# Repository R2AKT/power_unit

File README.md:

License addendum - https://github.com/R2AKT/power_unit/blob/main/Addendum.txt
# power_unit

Power control unit. For Mega-80 (Mega-580) DIY 8-bit micro-computer - https://github.com/R2AKT/Mega-80.
ATX PSU control based on 'ISA 8-bit Backplane' (https://github.com/skiselev/isa8_backplane).

Status - Tested.

Плата питания. Для самодельной 8-битной микро-ЭВМ - https://github.com/R2AKT/Mega-80.
Управление блоком питания ATX на основе 'ISA 8-bit Backplane' (https://github.com/skiselev/isa8_backplane).

Статус - Проверено.

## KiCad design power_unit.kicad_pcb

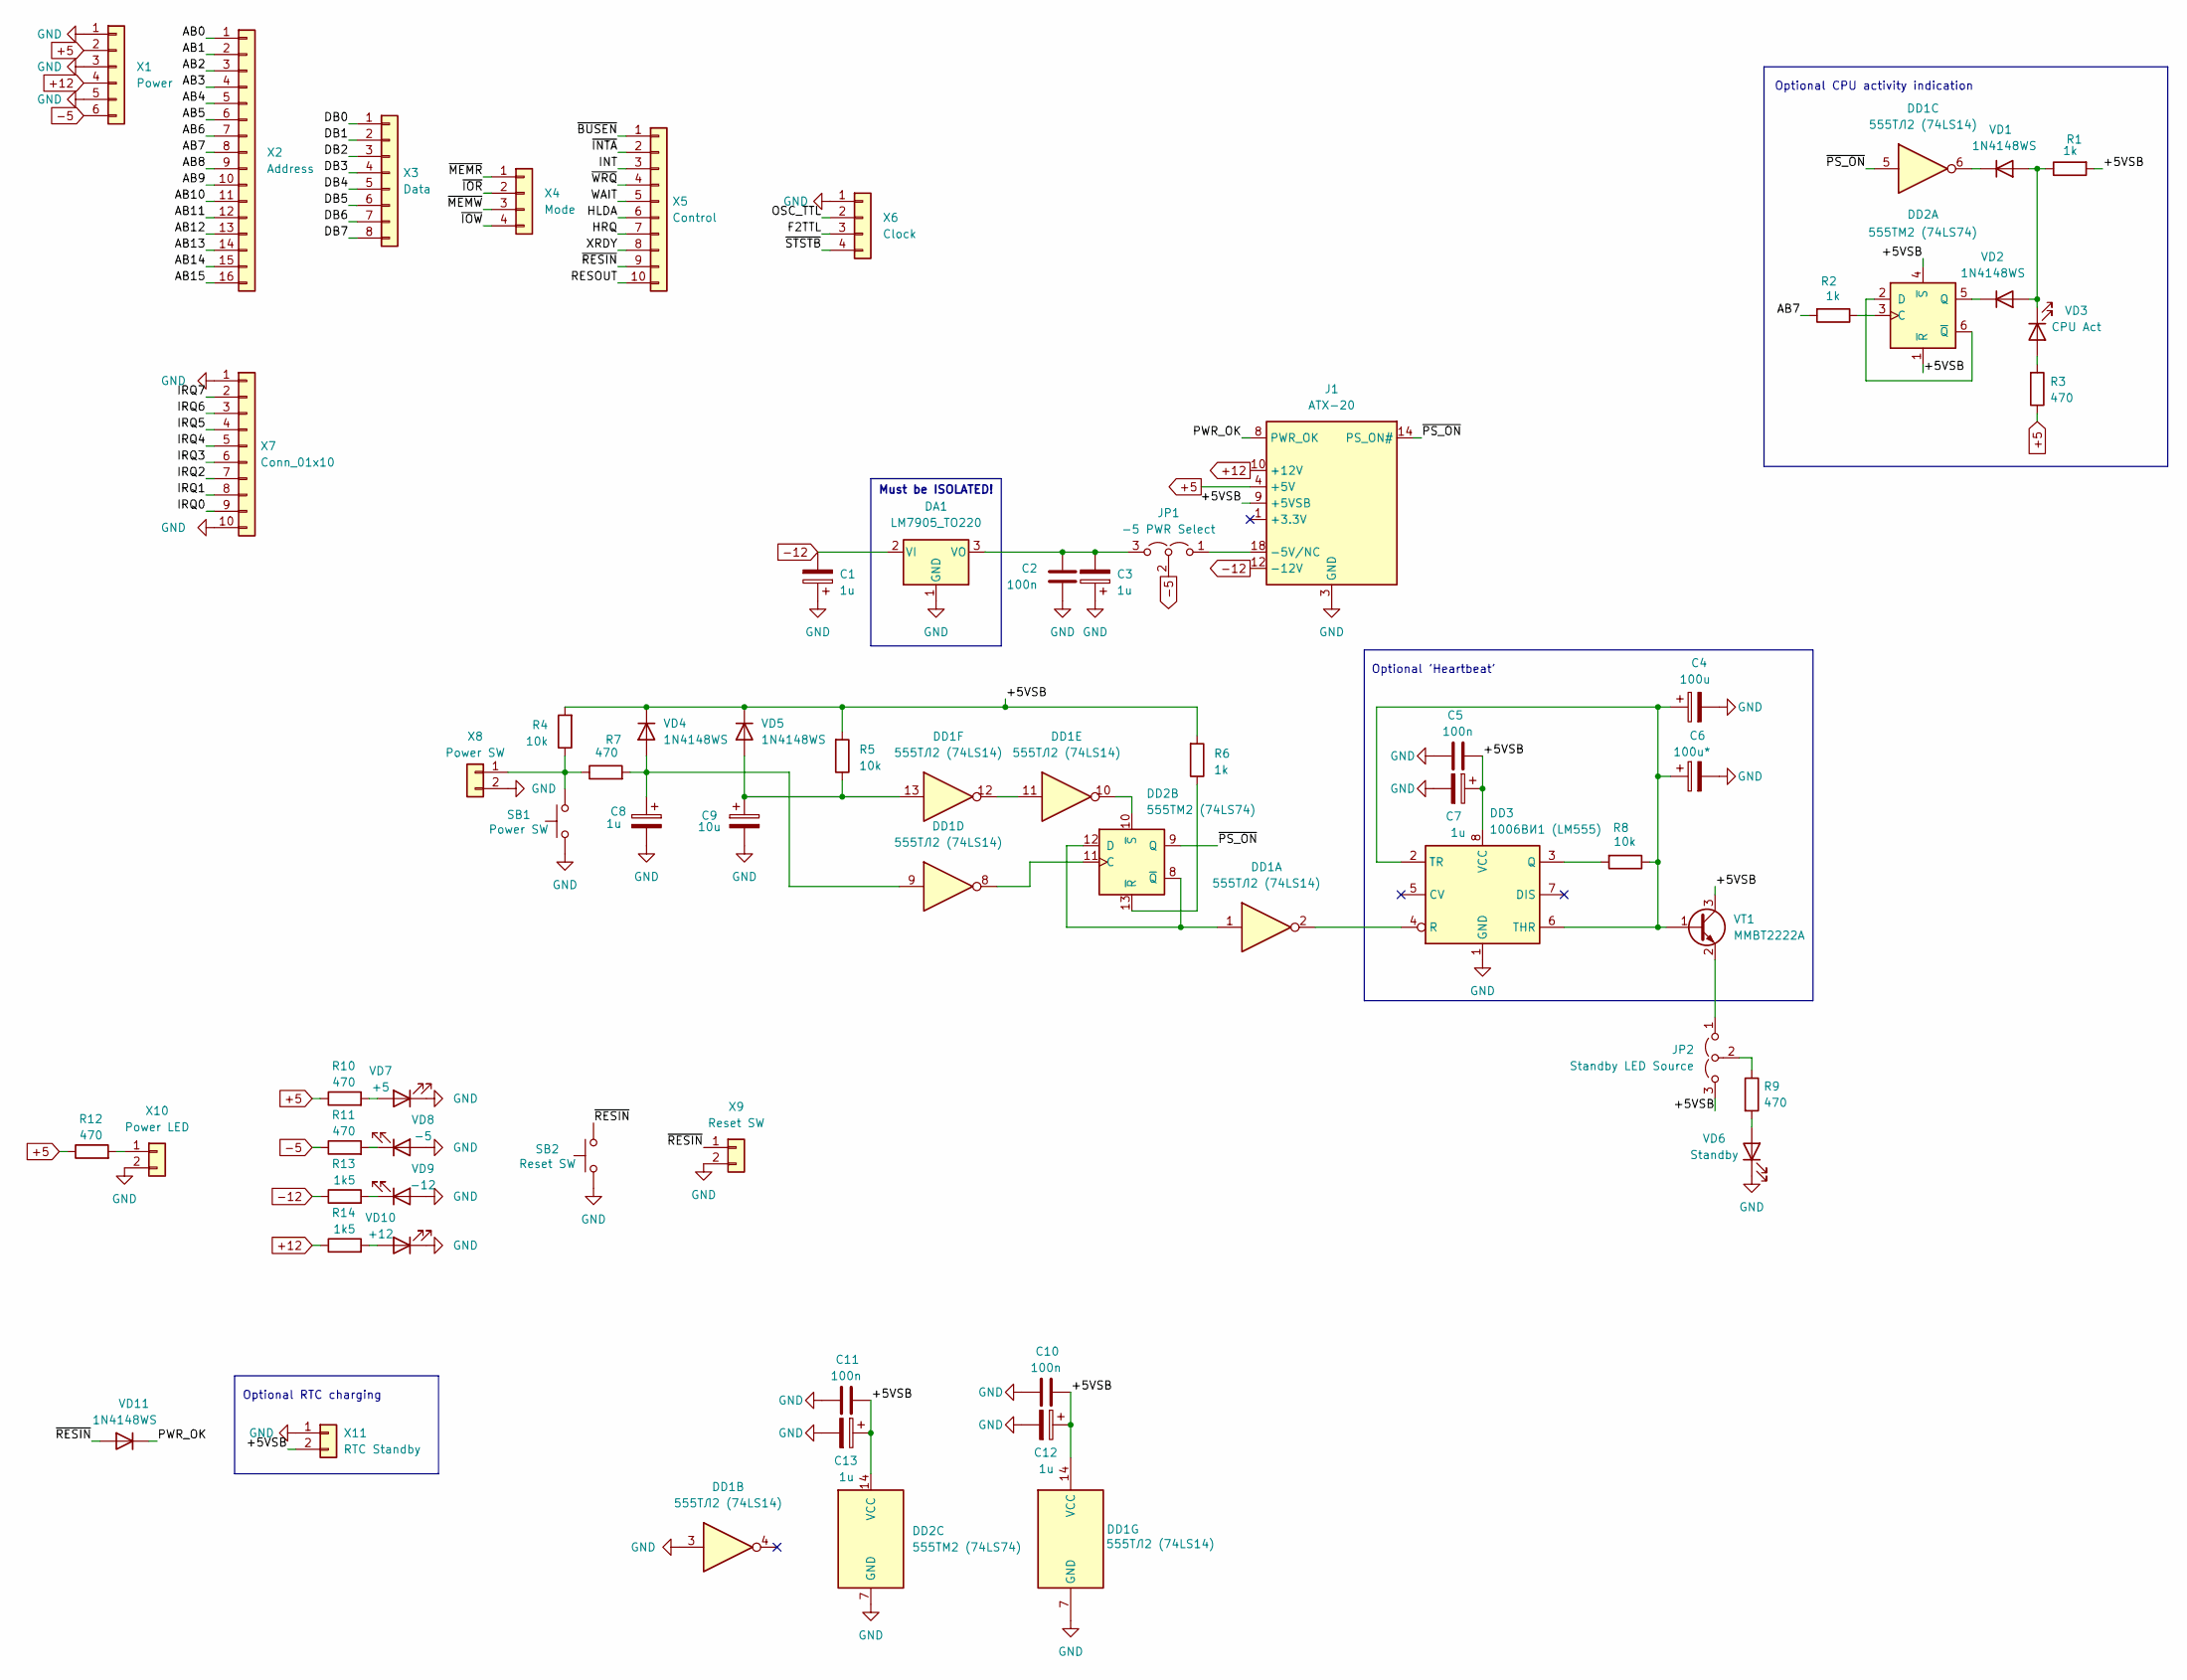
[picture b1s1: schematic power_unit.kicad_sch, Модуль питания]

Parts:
C1, C3, C7, C8, C12, C13: 1u; CP_EIA-3216-18_Kemet-A_Pad1.58x1.35mm_HandSolder
C2, C5, C10, C11: 100n; C_0805_2012Metric_Pad1.18x1.45mm_HandSolder
C4: 100u; CP_EIA-3528-21_Kemet-B_Pad1.50x2.35mm_HandSolder
C6: 100u*; CP_EIA-3528-21_Kemet-B_Pad1.50x2.35mm_HandSolder
C9: 10u; CP_EIA-3216-18_Kemet-A_Pad1.58x1.35mm_HandSolder
DA1: LM7905_TO220; TO-220-3_Horizontal_TabDown
DD1: 555ТЛ2 (74LS14); DIP-14_W7.62mm_Socket_LongPads
DD2: 555ТМ2 (74LS74); DIP-14_W7.62mm_Socket_LongPads
DD3: 1006ВИ1 (LM555); DIP-8_W7.62mm_Socket_LongPads
J1: ATX-20
JP1: -5 PWR Select; PinHeader_1x03_P2.54mm_Vertical
JP2: Standby LED Source; SolderJumper-3_P1.3mm_Open_RoundedPad1.0x1.5mm
R1, R2, R6: 1k; R_0805_2012Metric_Pad1.20x1.40mm_HandSolder
R3, R7, R9, R10, R11, R12: 470; R_0805_2012Metric_Pad1.20x1.40mm_HandSolder
R4, R5, R8: 10k; R_0805_2012Metric_Pad1.20x1.40mm_HandSolder
R13, R14: 1k5; R_0805_2012Metric_Pad1.20x1.40mm_HandSolder
SB1: Power SW; SW_PUSH_6mm
SB2: Reset SW; SW_PUSH_6mm
VD1, VD2, VD4, VD5, VD11: 1N4148WS; D_SOD-323_HandSoldering
VD3: CPU Act; LED_0805_2012Metric_Pad1.15x1.40mm_HandSolder
VD6: Standby; LED_0805_2012Metric_Pad1.15x1.40mm_HandSolder
VD7: +5; LED_0805_2012Metric_Pad1.15x1.40mm_HandSolder
VD8: -5; LED_0805_2012Metric_Pad1.15x1.40mm_HandSolder
VD9: -12; LED_0805_2012Metric_Pad1.15x1.40mm_HandSolder
VD10: +12; LED_0805_2012Metric_Pad1.15x1.40mm_HandSolder
VT1: MMBT2222A; SOT-23
X1: Power; PinSocket_1x06_P2.54mm_Vertical
X2: Address; PinSocket_1x16_P2.54mm_Vertical
X3: Data; PinSocket_1x08_P2.54mm_Vertical
X4: Mode; PinSocket_1x04_P2.54mm_Vertical
X5: Control; PinSocket_1x10_P2.54mm_Vertical
X6: Clock; PinSocket_1x04_P2.54mm_Vertical
X7: Conn_01x10; PinHeader_1x10_P2.54mm_Vertical
X8: Power SW; PinHeader_1x02_P2.54mm_Vertical
X9: Reset SW; PinHeader_1x02_P2.54mm_Vertical
X10: Power LED; PinHeader_1x02_P2.54mm_Vertical
X11: RTC Standby; PinSocket_1x02_P2.54mm_Vertical

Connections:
+5: J1.4 (+5V), J1.6 (+5V), J1.19 (+5V), J1.20 (+5V), R3.1, R10.1, R12.1, X1.2
+12: J1.10 (+12V), R14.1, X1.4
-5: JP1.2 (C), R11.1, X1.6
-12: C1.2, DA1.2 (VI), J1.12 (-12V), R13.1
/+5VSB: C5.1, C7.1, C10.1, C11.1, C12.1, C13.1, DD1.14 (VCC), DD2.1 (~R), DD2.4 (~S), DD2.14 (VCC), DD3.8 (VCC), J1.9 (+5VSB), JP2.3 (B), R1.2, R4.2, R5.2, R6.2, VD4.1 (K), VD5.1 (K), VT1.3 (C), X11.2
/AB0: X2.1
/AB1: X2.2
/AB2: X2.3
/AB3: X2.4
/AB4: X2.5
/AB5: X2.6
/AB6: X2.7
/AB7: R2.2, X2.8
/AB8: X2.9
/AB9: X2.10
/AB10: X2.11
/AB11: X2.12
/AB12: X2.13
/AB13: X2.14
/AB14: X2.15
/AB15: X2.16
/DB0: X3.1
/DB1: X3.2
/DB2: X3.3
/DB3: X3.4
/DB4: X3.5
/DB5: X3.6
/DB6: X3.7
/DB7: X3.8
/F2TTL: X6.3
/HLDA: X5.6
/HRQ: X5.7
/INT: X5.3
/IRQ0: X7.9
/IRQ1: X7.8
/IRQ2: X7.7
/IRQ3: X7.6
/IRQ4: X7.5
/IRQ5: X7.4
/IRQ6: X7.3
/IRQ7: X7.2
/OSC_TTL: X6.2
/PWR_OK: J1.8 (PWR_OK), VD11.1 (K)
/RESOUT: X5.10
/WAIT: X5.5
/XRDY: X5.8
/~BUSEN: X5.1
/~INTA: X5.2
/~IOR: X4.2
/~IOW: X4.4
/~MEMR: X4.1
/~MEMW: X4.3
/~PS_ON: DD1.5, DD2.9 (Q), J1.14 (PS_ON#)
/~RESIN: SB2.2, VD11.2 (A), X5.9, X9.1
/~STSTB: X6.4
/~WRQ: X5.4
GND: C1.1, C2.2, C3.1, C4.2, C5.2, C6.2, C7.2, C8.2, C9.2, C10.2, C11.2, C12.2, C13.2, DA1.1 (GND), DD1.3, DD1.7 (GND), DD2.7 (GND), DD3.1 (GND), J1.3 (GND), J1.5 (GND), J1.7 (GND), J1.13 (GND), J1.15 (GND), J1.16 (GND), J1.17 (GND), SB1.1, SB2.1, VD6.1 (K), VD7.1 (K), VD8.2 (A), VD9.2 (A), VD10.1 (K), X1.1, X1.3, X1.5, X6.1, X7.1, X7.10, X8.2, X9.2, X10.2, X11.1; also elsewhere on the board
unnamed: C2.1, C3.2, DA1.3 (VO), JP1.3 (B)
unnamed: DD1.11, DD1.12
unnamed: DD2.3 (C), R2.1
unnamed: DD2.2 (D), DD2.6 (~Q)
unnamed: DD2.5 (Q), VD2.1 (K)
unnamed: DD1.8, DD2.11 (C)
unnamed: DD1.1, DD2.8 (~Q), DD2.12 (D)
unnamed: DD2.13 (~R), R6.1
unnamed: DD1.10, DD2.10 (~S)
unnamed: DD3.3 (Q), R8.2
unnamed: DD1.2, DD3.4 (R)
unnamed: C4.1, C6.1, DD3.2 (TR), DD3.6 (THR), R8.1, VT1.1 (B)
unnamed: J1.18 (-5V/NC), JP1.1 (A)
unnamed: JP2.1 (A), VT1.2 (E)
unnamed: JP2.2 (C), R9.1
unnamed: R1.1, VD1.2 (A), VD2.2 (A), VD3.1 (K)
unnamed: DD1.6, VD1.1 (K)
unnamed: R3.2, VD3.2 (A)
unnamed: C8.1, DD1.9, R7.2, VD4.2 (A)
unnamed: C9.1, DD1.13, R5.1, VD5.2 (A)
unnamed: R9.2, VD6.2 (A)
unnamed: R10.2, VD7.2 (A)
unnamed: R11.2, VD8.1 (K)
unnamed: R13.2, VD9.1 (K)
unnamed: R14.2, VD10.2 (A)
unnamed: R4.1, R7.1, SB1.2, X8.1
unnamed: R12.2, X10.1

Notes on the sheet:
Optional 'Heartbeat'
Optional CPU activity indication
Must be ISOLATED!
Optional RTC charging

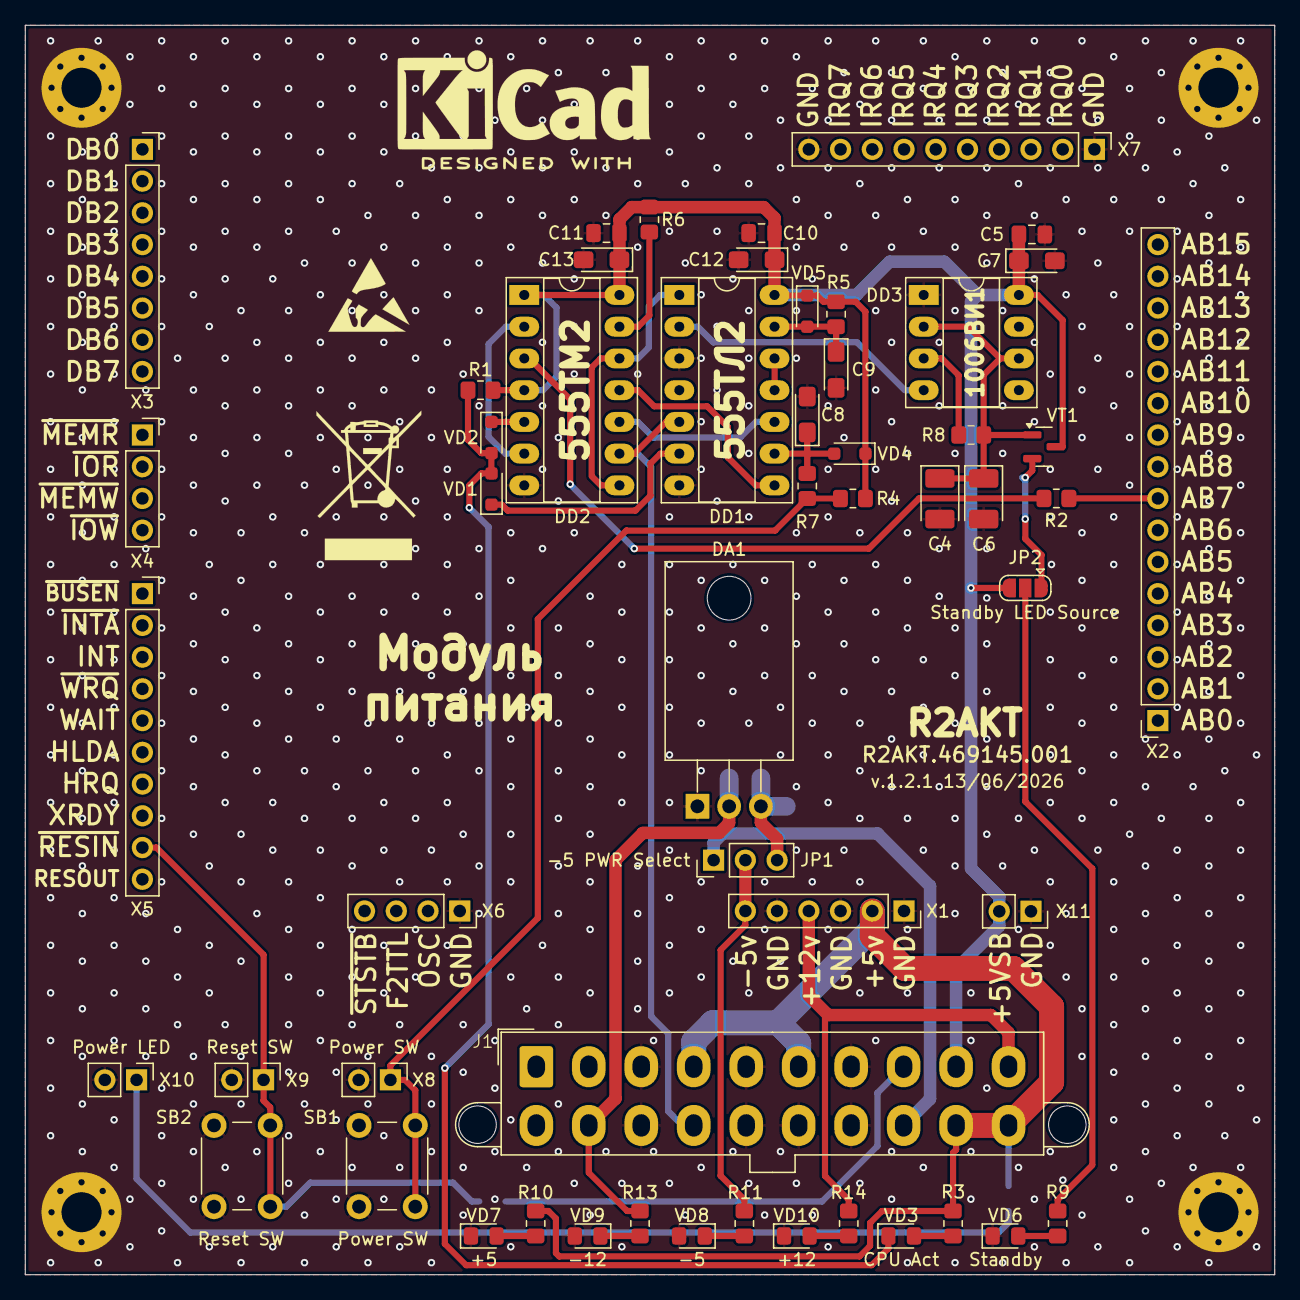
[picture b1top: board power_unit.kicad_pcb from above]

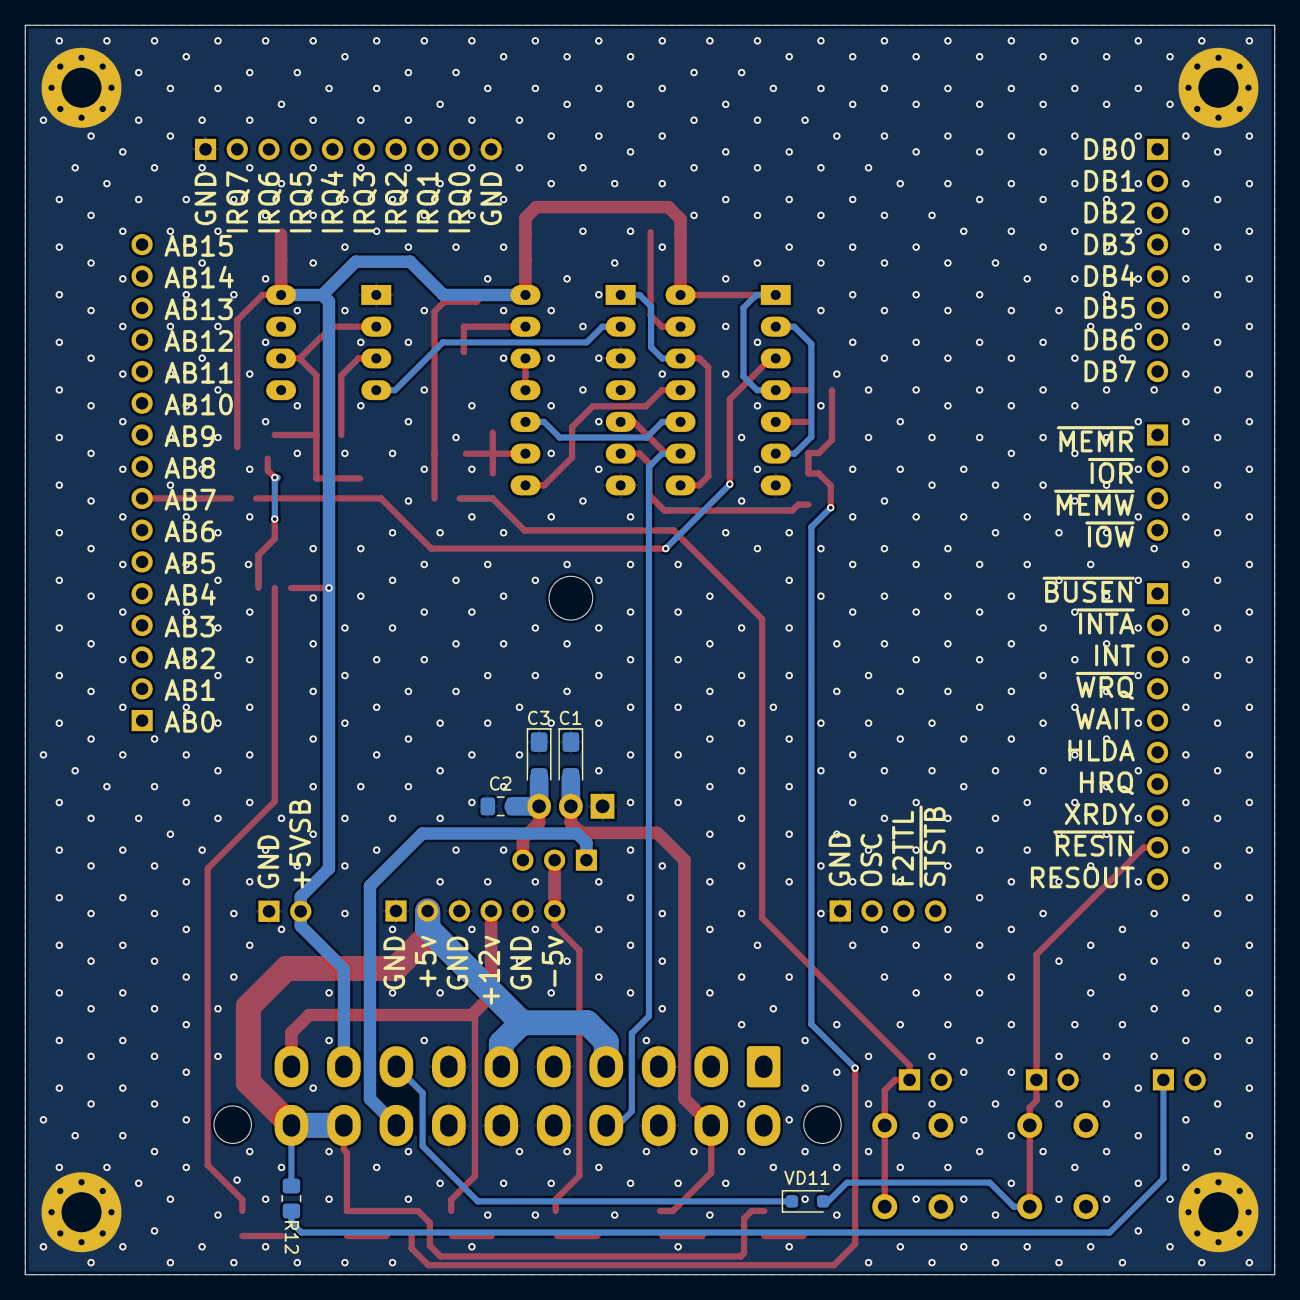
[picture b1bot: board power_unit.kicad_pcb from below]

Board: 2 copper layers, 100.0 x 100.0 mm, 63 parts (5 on the bottom side), 37 nets.

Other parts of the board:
H1, H2, H3, H4: MountingHole_Pad; MountingHole_3.2mm_M3_Pad_Via

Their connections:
GND: H1.1, H2.1, H3.1, H4.1; also elsewhere on the board

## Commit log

2026-03-23 Add files via upload
    Removed +5V LVR, added connection 'PG_OK' to 'ResIn'.
    Удалён линейный стабилизатор +5В, добавлено соединение 'PG_OK' с 'ResIn'.
2026-06-12 Update
    Fix footprint's, change optional shematic, add comment's

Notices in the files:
README.md:
License: MIT
